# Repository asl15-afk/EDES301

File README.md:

# EDES 301
Repository for EDES301 course work

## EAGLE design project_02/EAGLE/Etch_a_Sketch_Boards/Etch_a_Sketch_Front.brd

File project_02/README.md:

For this project I designed an Etch-a-sketch PCB. I used a PocketBeagle, USB port, 3 LEDs (red, blue, green), 2 button, 2 potentiometer and an SPI display.

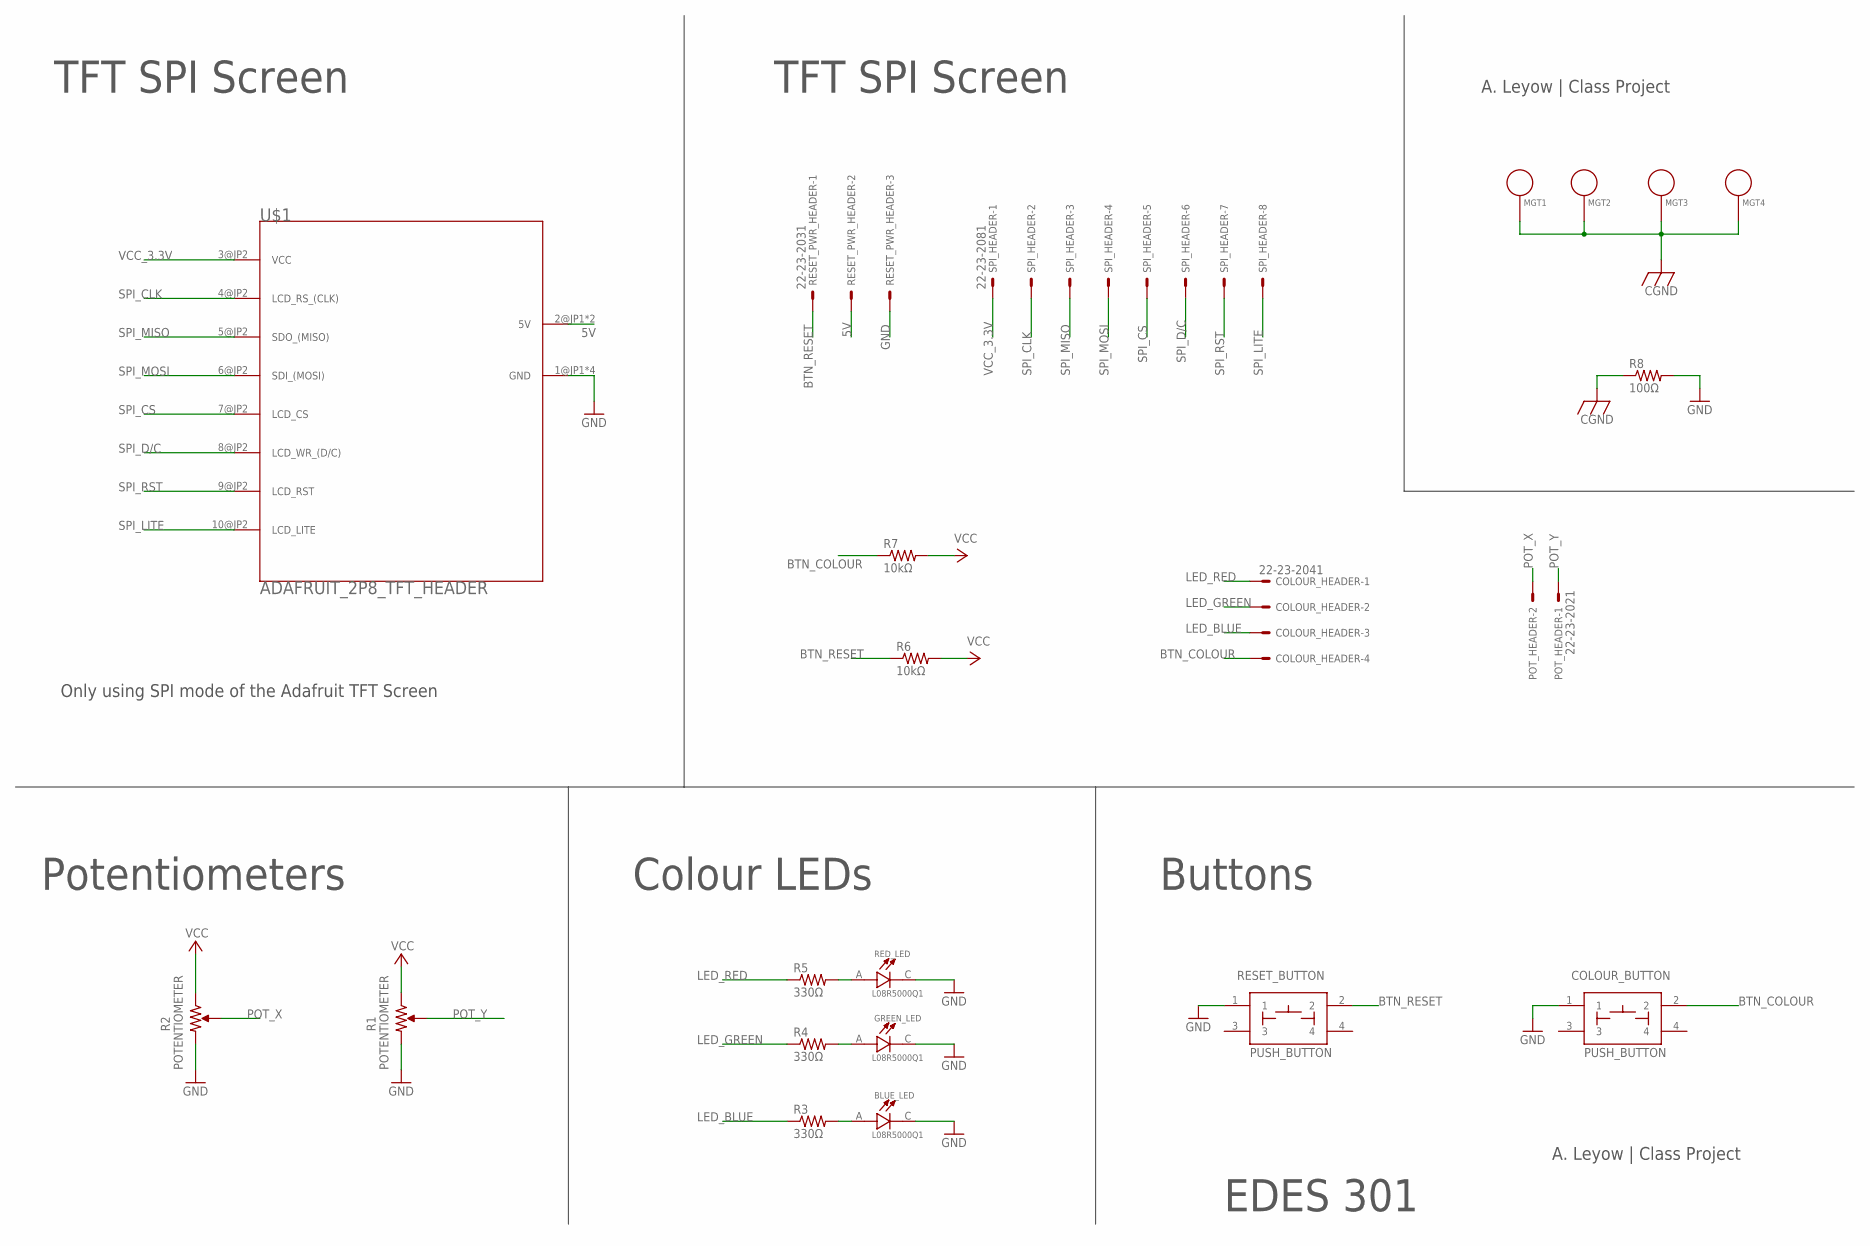
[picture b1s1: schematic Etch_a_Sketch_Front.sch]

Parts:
BLUE_LED: L08R5000Q1; LEDRD254W57D500H1070
COLOUR_BUTTON: PUSH_BUTTON; BUTTON_12.5MM
COLOUR_HEADER: 22-23-2041
GREEN_LED: L08R5000Q1; LEDRD254W57D500H1070
MGT1, MGT2, MGT3, MGT4: MOUNTING_HOLE
POT_HEADER: 22-23-2021
R1, R2: POTENTIOMETER; POT-PO90S
R3, R4, R5: 330Ω; R0805
R6, R7: 10kΩ; R0805
R8: 100Ω; R0805
RED_LED: L08R5000Q1; LEDRD254W57D500H1070
RESET_BUTTON: PUSH_BUTTON; BUTTON_12.5MM
RESET_PWR_HEADER: 22-23-2031
SPI_HEADER: 22-23-2081
U$1: ADAFRUIT_2P8_TFT_HEADER

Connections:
5V: RESET_PWR_HEADER.2, U$1.2@JP1 (5V), U$1.2@JP2 (5V)
BTN_COLOUR: COLOUR_BUTTON.2, COLOUR_HEADER.4, R7.1
BTN_RESET: R6.1, RESET_BUTTON.2, RESET_PWR_HEADER.1
CGND: MGT1.P$1, MGT2.P$1, MGT3.P$1, MGT4.P$1, R8.1
GND: BLUE_LED.C, COLOUR_BUTTON.1, GREEN_LED.C, R1.CW, R2.CW, R8.2, RED_LED.C, RESET_BUTTON.1, RESET_PWR_HEADER.3, U$1.1@JP1 (GND), U$1.1@JP2 (GND), U$1.11@JP2 (GND), U$1.12@JP1 (GND)
LED_BLUE: COLOUR_HEADER.3, R3.1
LED_GREEN: COLOUR_HEADER.2, R4.1
LED_RED: COLOUR_HEADER.1, R5.1
unnamed: BLUE_LED.A, R3.2
unnamed: GREEN_LED.A, R4.2
unnamed: R5.2, RED_LED.A
POT_X: POT_HEADER.2, R2.S
POT_Y: POT_HEADER.1, R1.S
SPI_CLK: SPI_HEADER.2, U$1.4@JP2 (LCD_RS_(CLK))
SPI_CS: SPI_HEADER.5, U$1.7@JP2 (LCD_CS)
SPI_D/C: SPI_HEADER.6, U$1.8@JP2 (LCD_WR_(D/C))
SPI_LITE: SPI_HEADER.8, U$1.10@JP2 (LCD_LITE)
SPI_MISO: SPI_HEADER.3, U$1.5@JP2 (SDO_(MISO))
SPI_MOSI: SPI_HEADER.4, U$1.6@JP2 (SDI_(MOSI))
SPI_RST: SPI_HEADER.7, U$1.9@JP2 (LCD_RST)
VCC: R1.CCW, R2.CCW, R6.2, R7.2
VCC_3.3V: SPI_HEADER.1, U$1.3@JP2 (VCC)

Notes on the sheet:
TFT SPI Screen
A. Leyow | Class Project
Buttons
Colour LEDs
Potentiometers
EDES 301
Only using SPI mode of the Adafruit TFT Screen

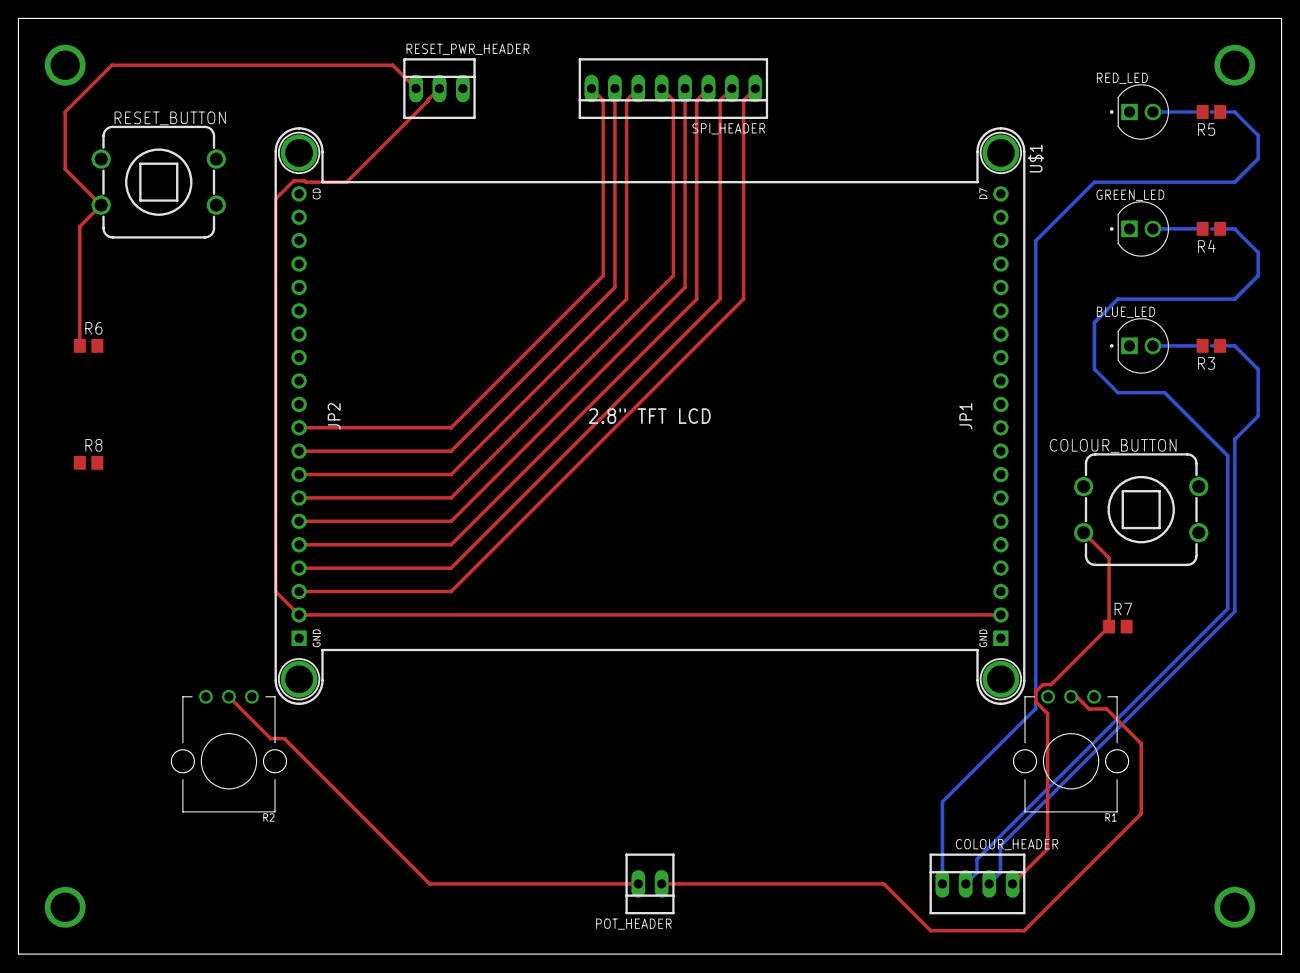
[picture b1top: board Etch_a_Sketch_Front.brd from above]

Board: 4 copper layers, 137.2 x 101.6 mm, 22 parts (0 on the bottom side), 22 nets.

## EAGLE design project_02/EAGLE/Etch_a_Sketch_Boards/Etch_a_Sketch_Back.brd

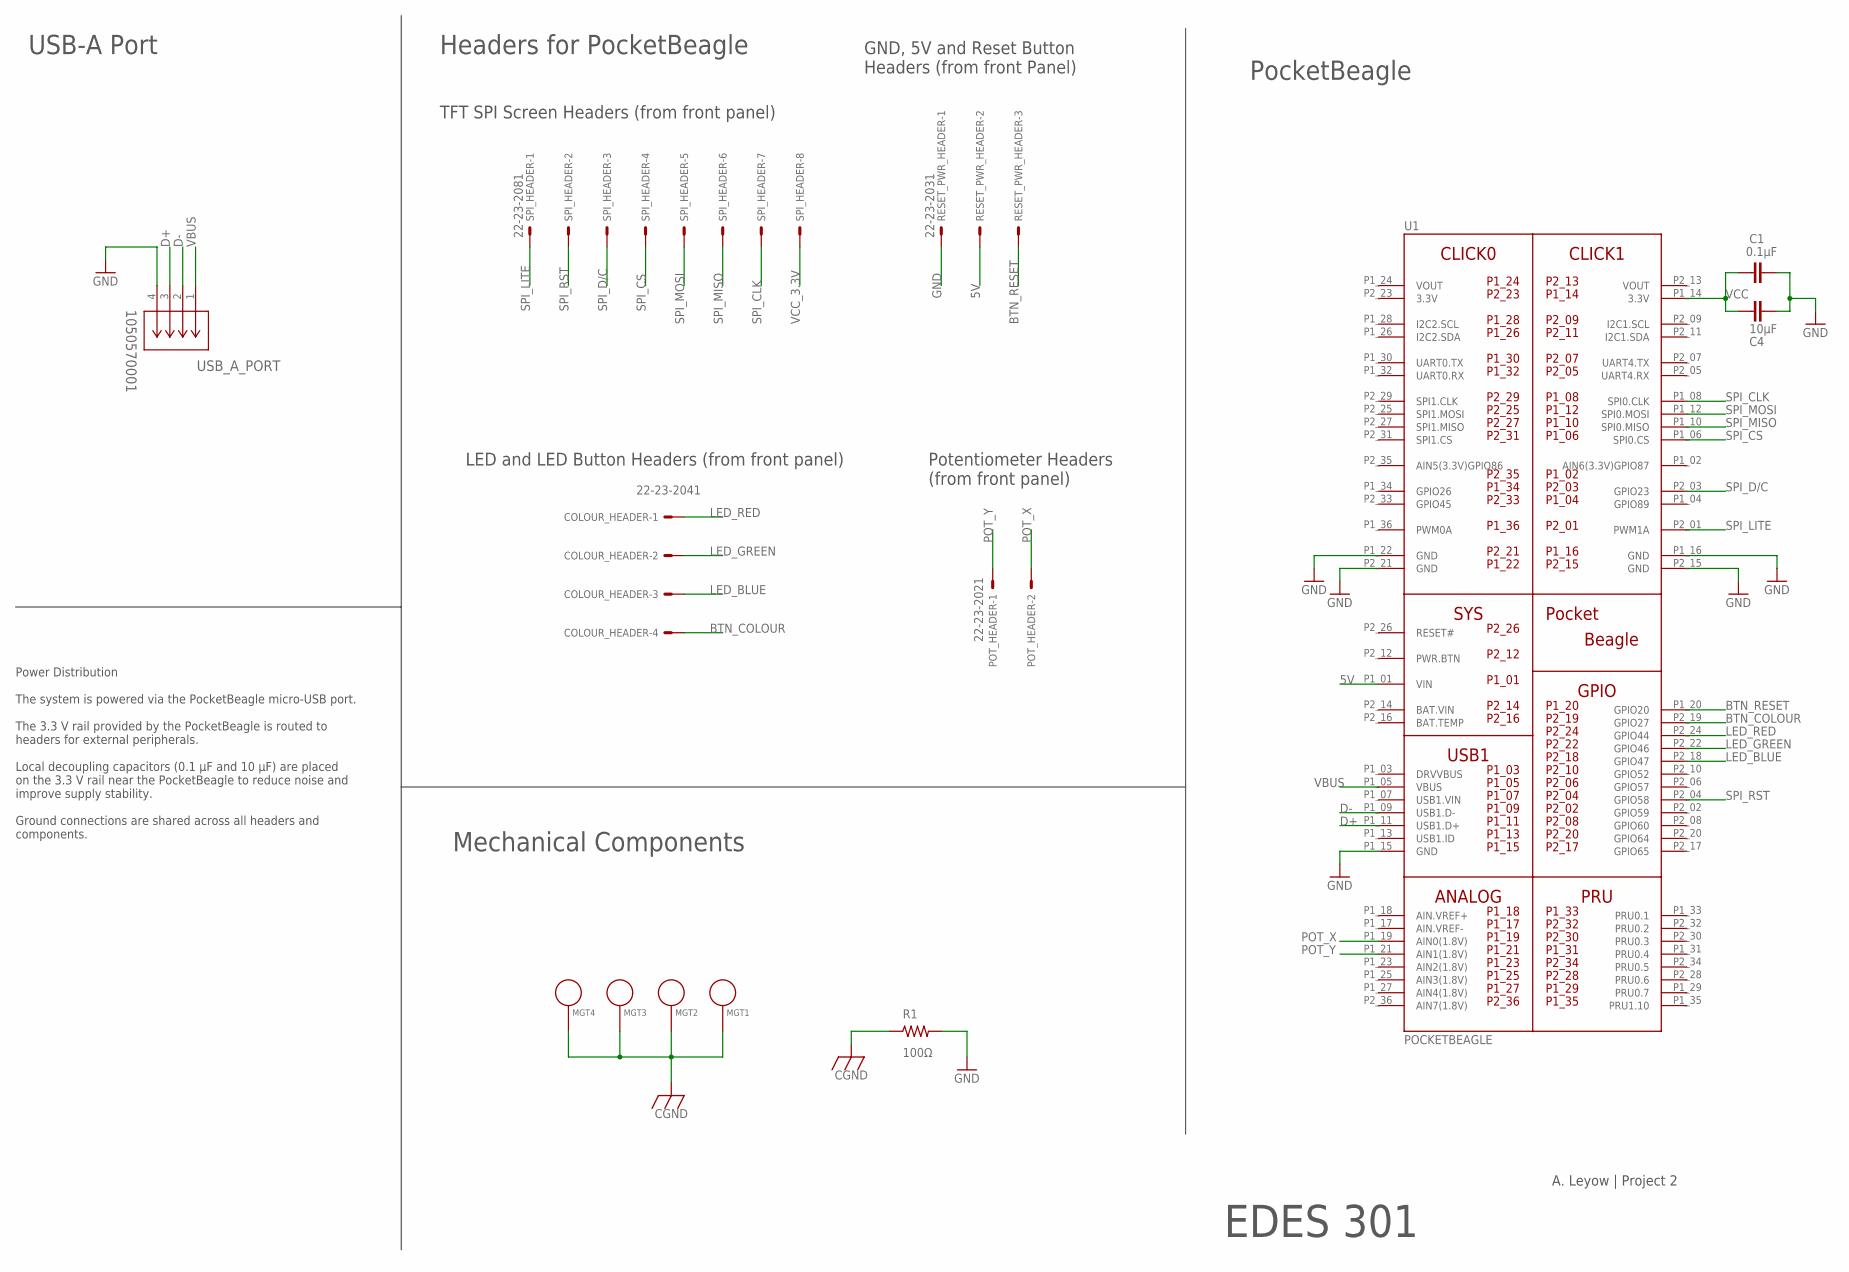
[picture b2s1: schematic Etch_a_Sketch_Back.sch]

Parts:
C1: 0.1µF; C0603
C4: 10µF; C0603
COLOUR_HEADER: 22-23-2041
MGT1, MGT2, MGT3, MGT4: MOUNTING_HOLE
POT_HEADER: 22-23-2021
R1: 100Ω; R0805
RESET_PWR_HEADER: 22-23-2031
SPI_HEADER: 22-23-2081
U1: POCKETBEAGLE
USB_A_PORT: 1050570001; CONN_1050570001_MOL

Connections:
3.3V: U1.P2_23 (3.3V)
5V: RESET_PWR_HEADER.2, U1.P1_01 (VIN)
BAT.VIN: U1.P2_14 (BAT.VIN)
BTN_COLOUR: COLOUR_HEADER.4, U1.P2_19 (GPIO27)
BTN_RESET: RESET_PWR_HEADER.3, U1.P1_20 (GPIO20)
CGND: MGT1.P$1, MGT2.P$1, MGT3.P$1, MGT4.P$1, R1.1
D+: U1.P1_11 (USB1.D+), USB_A_PORT.3
D-: U1.P1_09 (USB1.D-), USB_A_PORT.2
GND: C1.2, C4.2, R1.2, RESET_PWR_HEADER.1, U1.P1_15 (GND), U1.P1_16 (GND), U1.P1_22 (GND), U1.P2_15 (GND), U1.P2_21 (GND), USB_A_PORT.4
LED_BLUE: COLOUR_HEADER.3, U1.P2_18 (GPIO47)
LED_GREEN: COLOUR_HEADER.2, U1.P2_22 (GPIO46)
LED_RED: COLOUR_HEADER.1, U1.P2_24 (GPIO44)
POT_X: POT_HEADER.2, U1.P1_19 (AIN0(1.8V))
POT_Y: POT_HEADER.1, U1.P1_21 (AIN1(1.8V))
SPI_CLK: SPI_HEADER.7, U1.P1_08 (SPI0.CLK)
SPI_CS: SPI_HEADER.4, U1.P1_06 (SPI0.CS)
SPI_D/C: SPI_HEADER.3, U1.P2_03 (GPIO23)
SPI_LITE: SPI_HEADER.1, U1.P2_01 (PWM1A)
SPI_MISO: SPI_HEADER.6, U1.P1_10 (SPI0.MISO)
SPI_MOSI: SPI_HEADER.5, U1.P1_12 (SPI0.MOSI)
SPI_RST: SPI_HEADER.2, U1.P2_04 (GPIO58)
VBUS: U1.P1_05 (VBUS), USB_A_PORT.1
VCC: C1.1, C4.1, U1.P1_14 (3.3V)
VCC_3.3V: SPI_HEADER.8
VOUT: U1.P1_24 (VOUT), U1.P2_13 (VOUT)

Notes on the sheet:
USB-A Port
Headers for PocketBeagle
Mechanical Components
PocketBeagle
EDES 301
A. Leyow | Project 2
TFT SPI Screen Headers (from front panel)
GND, 5V and Reset Button
Headers (from front Panel)
LED and LED Button Headers (from front panel)
Potentiometer Headers
(from front panel)
Power Distribution The system is powered via the PocketBeagle micro-USB port. The 3.3 V rail provided by the PocketBeagle is routed to headers for external peripherals. Local decoupling capacitors (0.1 µF and 10 µF) are placed on the 3.3 V rail near the PocketBeagle to reduce noise and improve supp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

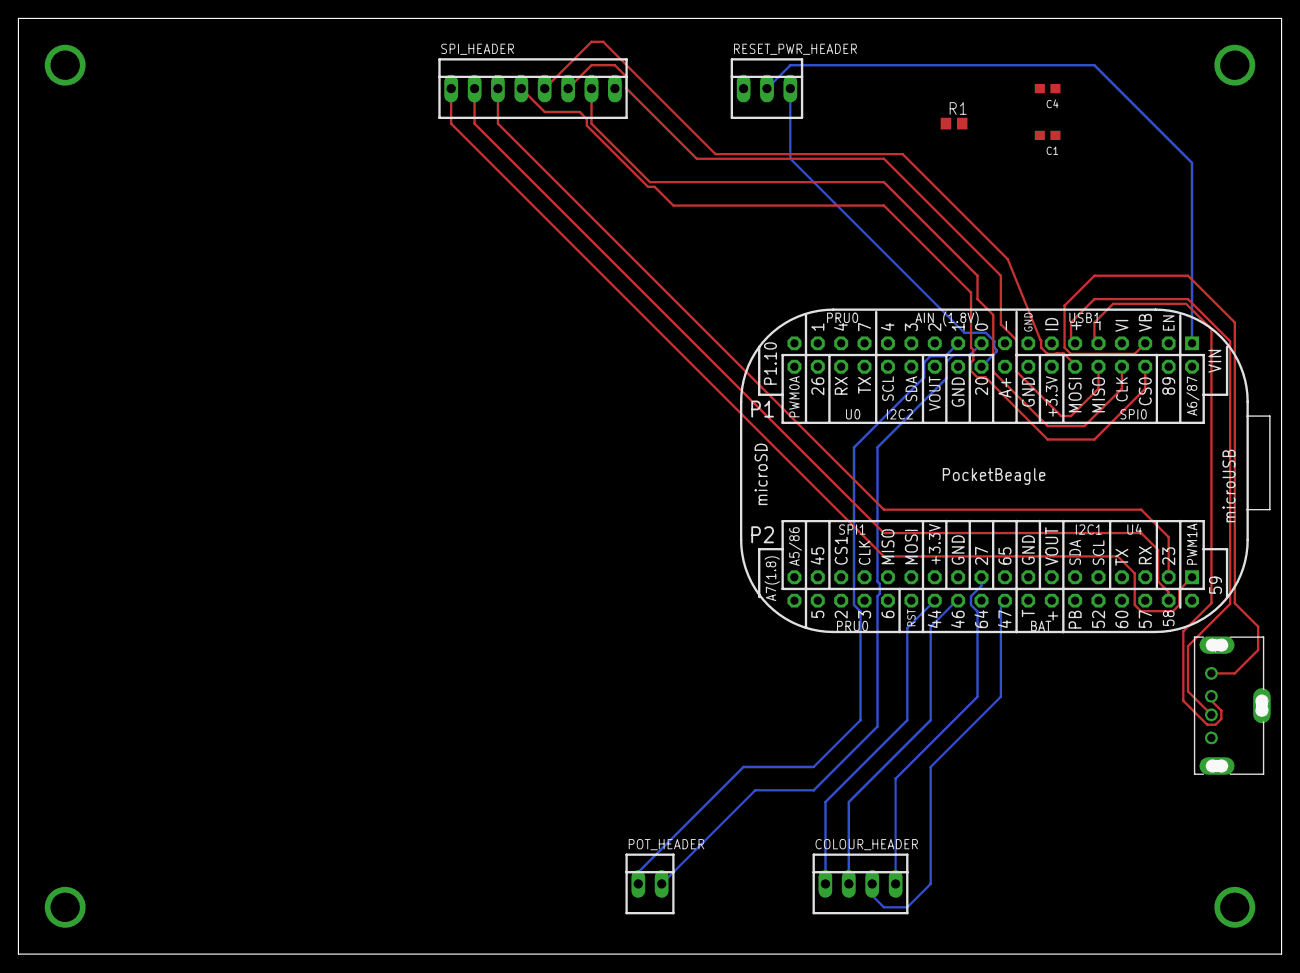
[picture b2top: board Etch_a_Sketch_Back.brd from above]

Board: 4 copper layers, 137.2 x 101.6 mm, 13 parts (0 on the bottom side), 22 nets.

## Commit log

2025-09-23 Updating README.md
2025-09-30 Create temp.txt
    Creating temp.txt for q1c of assignment 3
2025-10-07 Support for python 2
2025-10-07 Commiting the python simple calculator done in class
2025-10-07 Commiting all changes to simple_calc
2025-10-07 EDES301 HW4 Q1 & Q2 submission push
2025-12-16 Create Library
    created project 2 folder, eagle subfolder and library file
2025-12-16 Create Schematics
    creating schematics file
2025-12-16 Rename Library to Project_2_Library
2025-12-16 Rename Schematics to Project_2_Schematics
2025-12-16 Create Project_2_Layout
2025-12-16 Added Project 2 PPT
    Added Project 2 PPT including Mechanical Block Diagram
2025-12-19 Added Project_2 PCB Back Panel pdf
2025-12-19 Rename Etch_a_Sketch_Back.pdf to Etch_a_Sketch_Back_Schematic.pdf
2025-12-19 Added Project 2 Front PCB Panel Schematic
2025-12-19 Added Screenshot of Bottom Layer of Back PCB Panel
2025-12-19 Added top layer Screenshot of EaS PCB Back Panel
2025-12-19 Rename Etch_a_Sketch_Front.pdf to Etch_a_Sketch_Front_Schematic.pdf
2025-12-19 Uploaded Etch_a_Sketch.lbr
2025-12-19 Uploaded Etch_a_Sketch_Schematics
2025-12-19 Uploaded Top Layer Front Panel of EaS PCB board
2025-12-19 Uploaded Bottom Layer Front Panel of EaS PCB board
2025-12-19 Uploaded Etch a Sketch Layout
2025-12-19 Create MFG
2025-12-19 Create CAM Outputs
2025-12-19 Uploading gerbers and CAM outputs
2025-12-19 Upload Bill of Materials
2025-12-19 Upload BOM csv
